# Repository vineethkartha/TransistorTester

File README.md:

# Transistor Tester
This cicuit is used to detect if a transistor is NPN or PNP.
If the transistor being tested is damaged, then either both LEDs might glow or none might glow.

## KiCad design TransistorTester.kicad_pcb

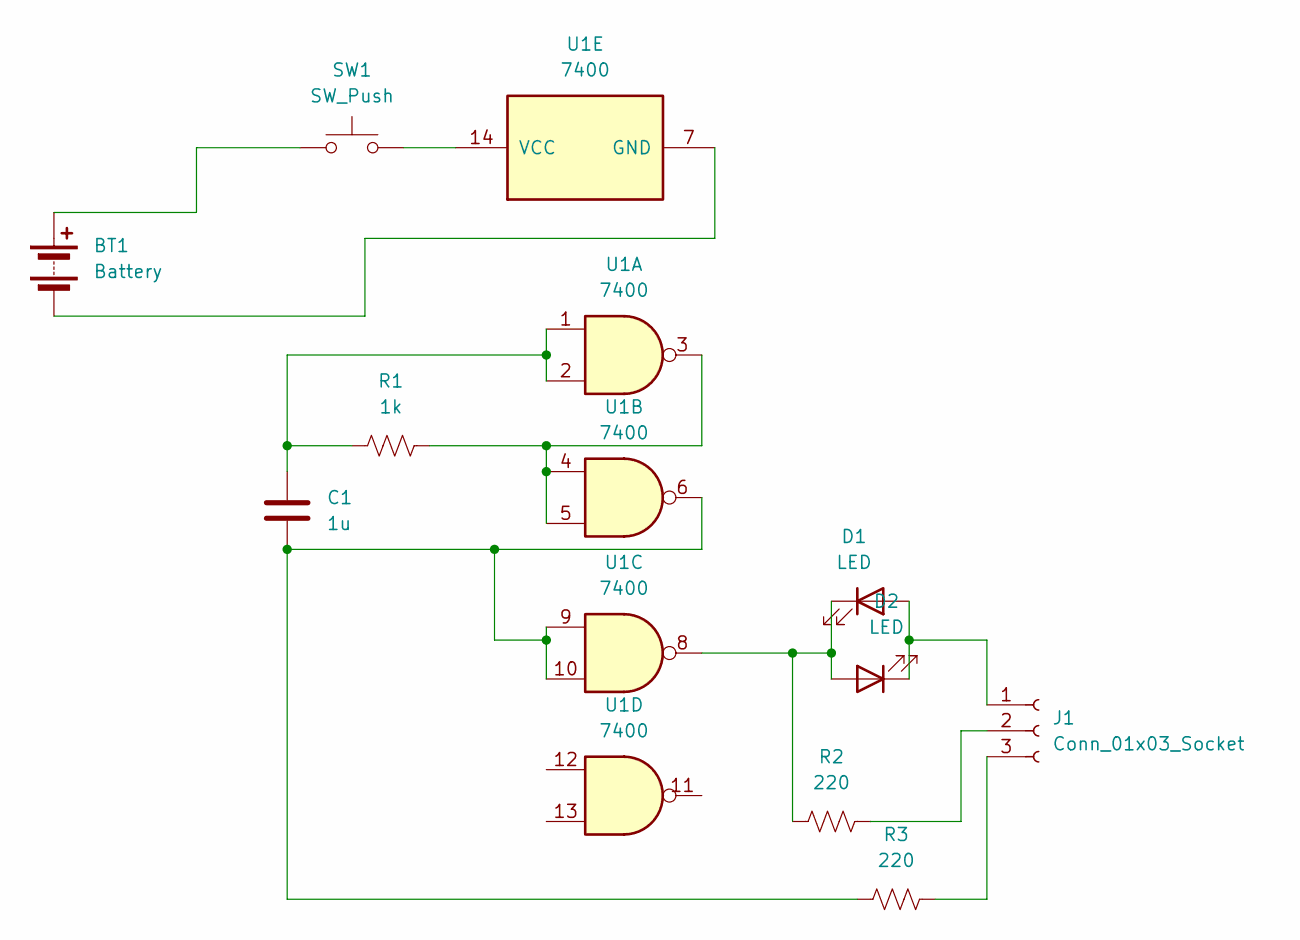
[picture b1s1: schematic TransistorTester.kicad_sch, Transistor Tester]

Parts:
BT1: Battery; PinHeader_1x02_P2.54mm_Vertical
C1: 1u; C_Disc_D3.0mm_W1.6mm_P2.50mm
D1, D2: LED; LED_D5.0mm
J1: Conn_01x03_Socket; PinSocket_1x03_P2.54mm_Vertical
R1: 1k; R_Axial_DIN0207_L6.3mm_D2.5mm_P7.62mm_Horizontal
R2, R3: 220; R_Axial_DIN0207_L6.3mm_D2.5mm_P7.62mm_Horizontal
SW1: SW_Push; SW_PUSH_6mm_H5mm
U1: 7400; DIP-14_W7.62mm_Socket

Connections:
unnamed: BT1.1 (+), SW1.1
unnamed: BT1.2 (-), U1.7 (GND)
unnamed: C1.1, R1.1, U1.1, U1.2
unnamed: C1.2, R3.1, U1.6, U1.9, U1.10
unnamed: D1.2 (A), D2.1 (K), J1.1
unnamed: D1.1 (K), D2.2 (A), R2.2, U1.8
unnamed: J1.2, R2.1
unnamed: J1.3, R3.2
unnamed: R1.2, U1.3, U1.4, U1.5
unnamed: SW1.2, U1.14 (VCC)

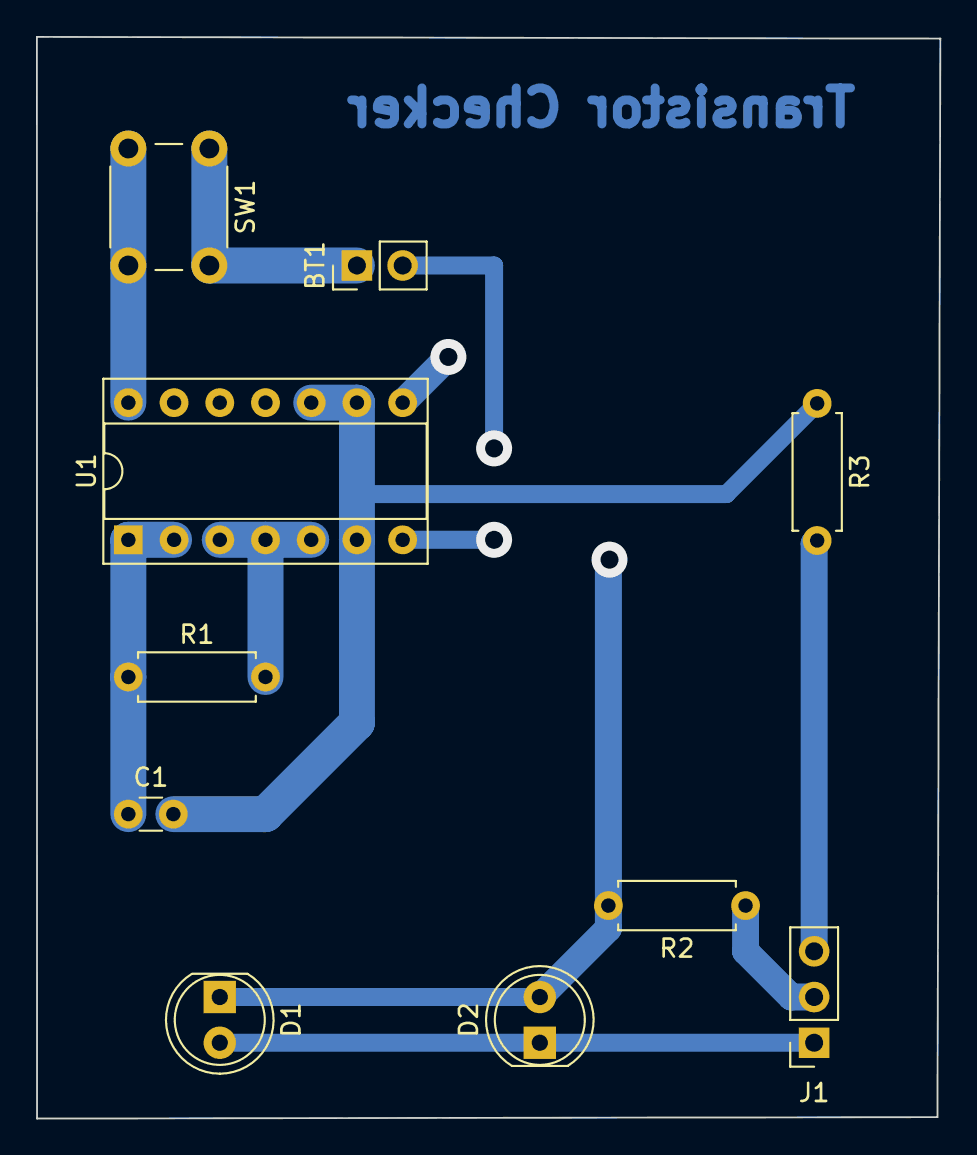
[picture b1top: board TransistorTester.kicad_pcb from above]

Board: 2 copper layers, 50.2 x 60.1 mm, 10 parts (0 on the bottom side), 10 nets.

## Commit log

2023-12-17 Initial Submission
